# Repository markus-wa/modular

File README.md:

# modular

Setup for my A/V project [S/AV/G](http://instagram.com/savg.av)

## Current Setup

See [ModularGrid](https://modulargrid.net/e/racks/view/2683365)

## WIP

- 2x DIY VGA Module (Breakout, Sync Generator & DDC EEPROM)
- DIY Preview Panel w/ 2x LCD

## Interesting Products

- [CBV002 by Syntonie](https://syntonie.fr/products/cbv002-circuit-bent-video-delay)
- [Stable by Syntonie](https://syntonie.fr/products/stable)
- [Entree, Triple Video Distribution Amp, Rampes, Seuils, Solaire, Isohelie, RGB Encoder by Syntonie](https://syntonie.fr/products/rampes-ramp-generator-sync-extractor)
- [F4DER, AURAL SCAN & more by Video Headroom Systems](https://www.videoheadroom.systems/video-synthesizers/p/f4der)
- [Video Matrix Mixer & more by Reverse Landfill](https://www.reverselandfill.org/category/eurorack-video/)

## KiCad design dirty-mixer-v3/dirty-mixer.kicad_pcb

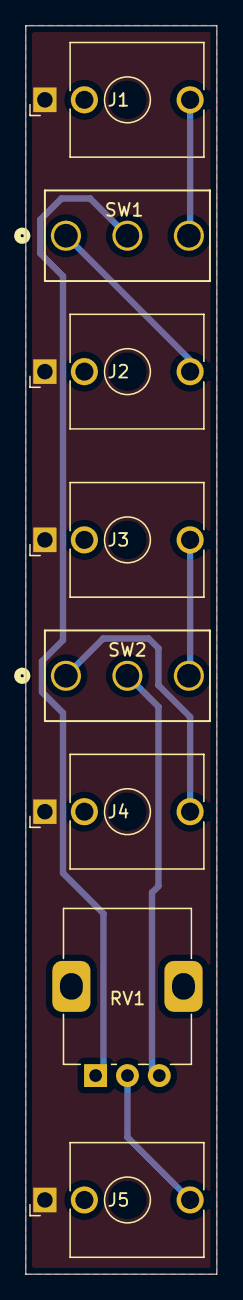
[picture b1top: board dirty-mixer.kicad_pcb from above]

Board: 2 copper layers, 15.0 x 98.0 mm, 8 parts (0 on the bottom side), 8 nets.

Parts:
J1, J2, J3, J4, J5: AudioJack2_SwitchT; Jack_3.5mm_QingPu_WQP-PJ398SM_Vertical_CircularHoles
RV1: R_Potentiometer; Potentiometer_Alps_RK09K_Single_Vertical
SW1, SW2: SW_SPDT; ANT13SEC_CRS

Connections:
GND: J1.S, J2.S, J3.S, J4.S, J5.S
unnamed: J5.T, RV1.2
unnamed: J2.T, SW1.1 (A)
unnamed: RV1.1, SW1.2 (B)
unnamed: J1.T, SW1.3 (C)
unnamed: J4.T, SW2.1 (A)
unnamed: RV1.3, SW2.2 (B)
unnamed: J3.T, SW2.3 (C)

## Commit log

2024-10-13 dirty mixer panel & arduino vsync generator code
2024-10-13 readme: add WIP section
2024-10-13 preview module panel
2024-10-13 vga io panel
2024-10-14 readme: gliss
2024-10-25 dirty mixer PCB
2025-02-06 av-pi code
2025-02-06 some pcb changes
2025-02-06 Bump golang.org/x/sys in /av-pi
    Bumps [golang.org/x/sys](https://github.com/golang/sys) from 0.0.0-20220319134239-a9b59b0215f8 to 0.1.0.
    - [Commits](https://github.com/golang/sys/commits/v0.1.0)
    ---
    updated-dependencies:
    - dependency-name: golang.org/x/sys
    dependency-type: indirect
2025-02-06 readme: ModularGrid link + pic
2025-02-09 make work with switch pro controller
2025-02-10 vlc sampler progress
2025-02-25 wip for BiG CHiP NRG
2025-02-25 fix midi controls
2025-02-26 dedupe some code and retry
2025-02-27 refactor
2025-02-27 fix compilation + zap log
2025-02-27 create playlists dir if not exists
2025-02-27 downgrade opengl requirement
2025-02-27 hud: embed font
2025-02-27 hud: fix font not loading
2025-02-27 Bump golang.org/x/image from 0.3.0 to 0.18.0 in /av-pi
    Bumps [golang.org/x/image](https://github.com/golang/image) from 0.3.0 to 0.18.0.
    - [Commits](https://github.com/golang/image/compare/v0.3.0...v0.18.0)
    ---
    updated-dependencies:
    - dependency-name: golang.org/x/image
    dependency-type: indirect
2025-02-27 dont error if screen cant be played
2025-02-27 try to fix vlc on pi
2025-02-27 fix mode double assigned
2025-02-27 reduce log spam
2025-02-27 dont send gate on ch=0 (CC channel)
2025-02-27 log btn presses
2025-02-27 dont send duplicate gates
2025-02-27 less spam
2025-02-27 fix 8bitdo mappings
2025-02-28 only change mode on down press not release
2025-02-28 skip unplayable media
2025-02-28 try to fix vlc sampler
2025-02-28 fix crash
2025-02-28 sampler: only toggle mode on press, not release
2025-02-28 remove dupe print
2025-02-28 fix mode print
2025-02-28 play stream list by default
2025-02-28 pi fixed, no reenc needed
2025-02-28 fullscreen
2025-02-28 midi: home opens default port
